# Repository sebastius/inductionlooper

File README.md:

# inductionlooper
Cheap Induction Loop using RJ45 UTP cables

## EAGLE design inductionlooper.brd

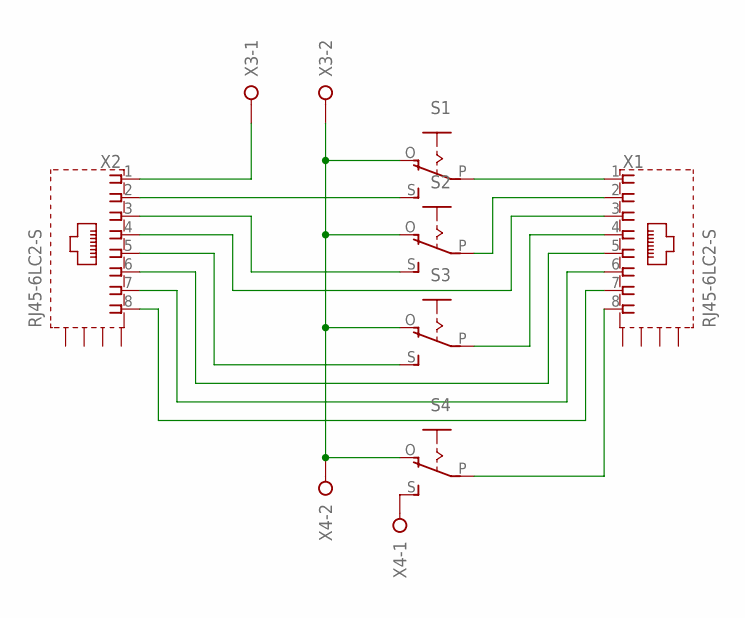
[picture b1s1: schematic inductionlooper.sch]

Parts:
S1, S2, S3, S4: EG1218S; EG1218
X1, X2: RJ45-6LC2-S; RJ45-SHIELD2
X3, X4: W237-02P; W237-132

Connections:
unnamed: X2.1, X3.1
unnamed: S1.P, X1.1
unnamed: S1.S, X2.2
unnamed: X1.5, X2.6
unnamed: S2.P, X1.2
unnamed: S2.S, X2.3
unnamed: X1.3, X2.4
unnamed: S3.P, X1.4
unnamed: S1.O, S2.O, S3.O, S4.O, X3.2, X4.2
unnamed: S3.S, X2.5
unnamed: X1.6, X2.7
unnamed: X1.7, X2.8
unnamed: S4.P, X1.8
unnamed: S4.S, X4.1

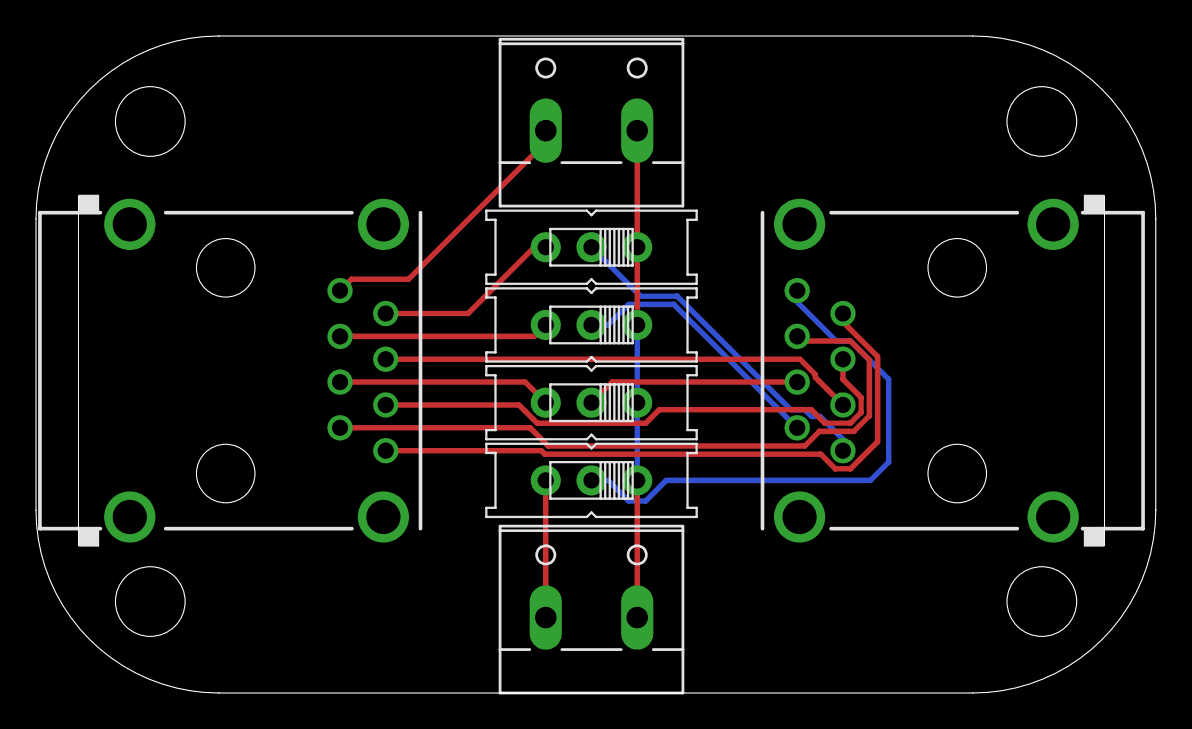
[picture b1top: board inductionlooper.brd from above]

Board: 2 copper layers, 62.2 x 36.5 mm, 8 parts (0 on the bottom side), 14 nets.

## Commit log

2020-02-22 First commit
    Should be fine
